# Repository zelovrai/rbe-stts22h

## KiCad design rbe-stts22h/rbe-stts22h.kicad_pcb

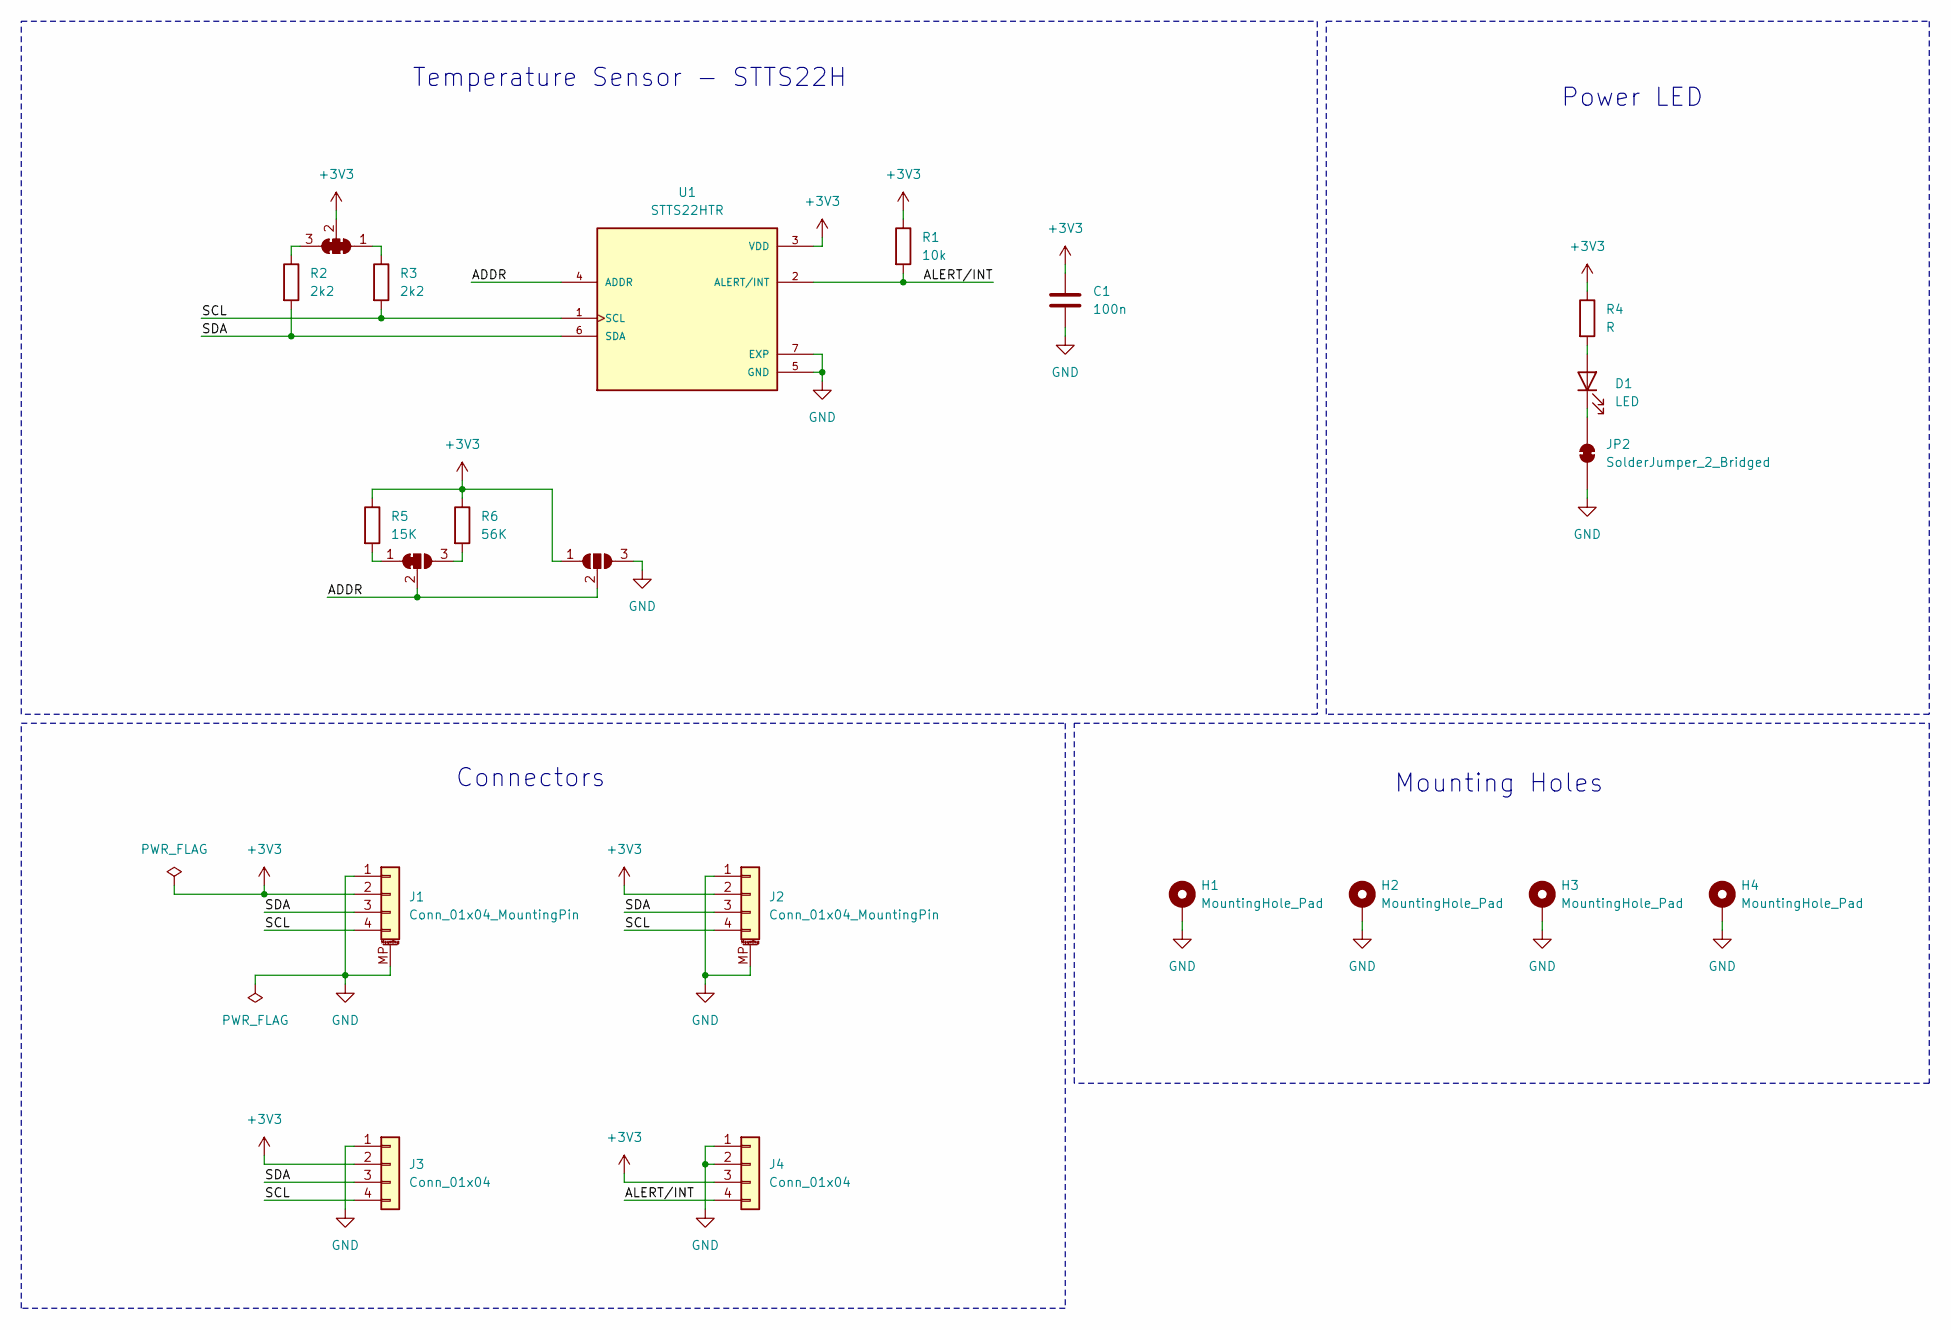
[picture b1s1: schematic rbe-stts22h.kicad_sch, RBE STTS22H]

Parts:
C1: 100n; C_0603_1608Metric
D1: LED; LED_0603_1608Metric
H1, H2, H3, H4: MountingHole_Pad; MountingHole_3.2mm_M3_Pad
J1, J2: Conn_01x04_MountingPin; JST_SH_SM04B-SRSS-TB_1x04-1MP_P1.00mm_Horizontal
J3, J4: Conn_01x04; PinSocket_1x04_P2.54mm_Vertical
JP1: SolderJumper_3_Bridged123; SolderJumper-3_P1.3mm_Bridged123_RoundedPad1.0x1.5mm
JP2: SolderJumper_2_Bridged; SolderJumper-2_P1.3mm_Bridged_RoundedPad1.0x1.5mm
JP3: SolderJumper_3_Bridged12; SolderJumper-3_P1.3mm_Bridged12_RoundedPad1.0x1.5mm
JP4: SolderJumper_3_Open; SolderJumper-3_P1.3mm_Open_RoundedPad1.0x1.5mm
R1: 10k; R_0603_1608Metric
R2, R3: 2k2; R_0603_1608Metric
R4: R; R_0603_1608Metric
R5: 15K; R_0603_1608Metric
R6: 56K; R_0603_1608Metric
U1: STTS22HTR; SON65P200X200X55-7N; PARTREV 7

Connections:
+3V3: C1.1, J1.2, J2.2, J3.2, J4.3, JP1.2 (C), JP4.1 (A), R1.1, R4.1, R5.1, R6.1, U1.3 (VDD)
/ADDR: JP3.2 (C), JP4.2 (C), U1.4 (ADDR)
/ALERT/INT: J4.4, R1.2, U1.2 (ALERT/INT)
/SCL: J1.4, J2.4, J3.4, R3.2, U1.1 (SCL)
/SDA: J1.3, J2.3, J3.3, R2.2, U1.6 (SDA)
GND: C1.2, H1.1 (1_1), H2.1 (1_1), H3.1 (1_1), H4.1 (1_1), J1.1, J1.MP (MountPin), J2.1, J2.MP (MountPin), J3.1, J4.1, J4.2, JP2.1 (A), JP4.3 (B), U1.5 (GND), U1.7 (EXP)
unnamed: D1.2 (A), R4.2
unnamed: D1.1 (K), JP2.2 (B)
unnamed: JP1.1 (A), R3.1
unnamed: JP1.3 (B), R2.1
unnamed: JP3.1 (A), R5.2
unnamed: JP3.3 (B), R6.2

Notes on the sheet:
Temperature Sensor - STTS22H
Power LED
Mounting Holes
Connectors

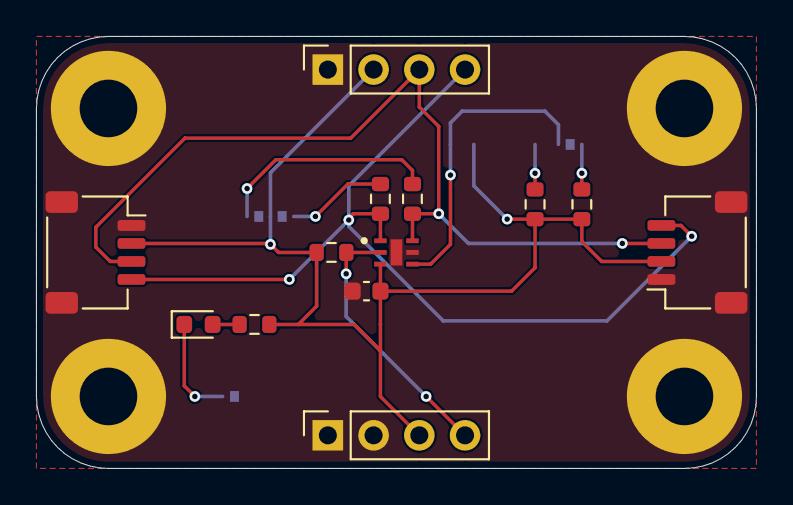
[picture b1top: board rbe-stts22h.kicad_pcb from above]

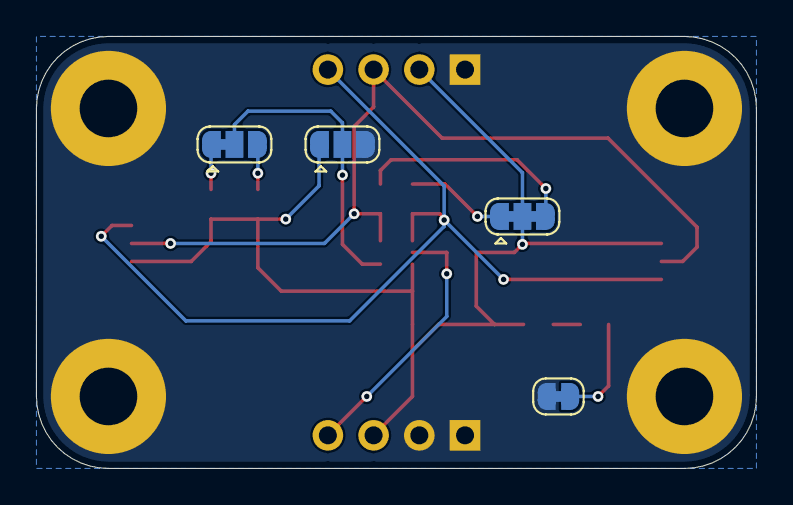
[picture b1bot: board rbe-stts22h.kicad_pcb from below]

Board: 2 copper layers, 40.0 x 24.0 mm, 21 parts (4 on the bottom side), 12 nets.
